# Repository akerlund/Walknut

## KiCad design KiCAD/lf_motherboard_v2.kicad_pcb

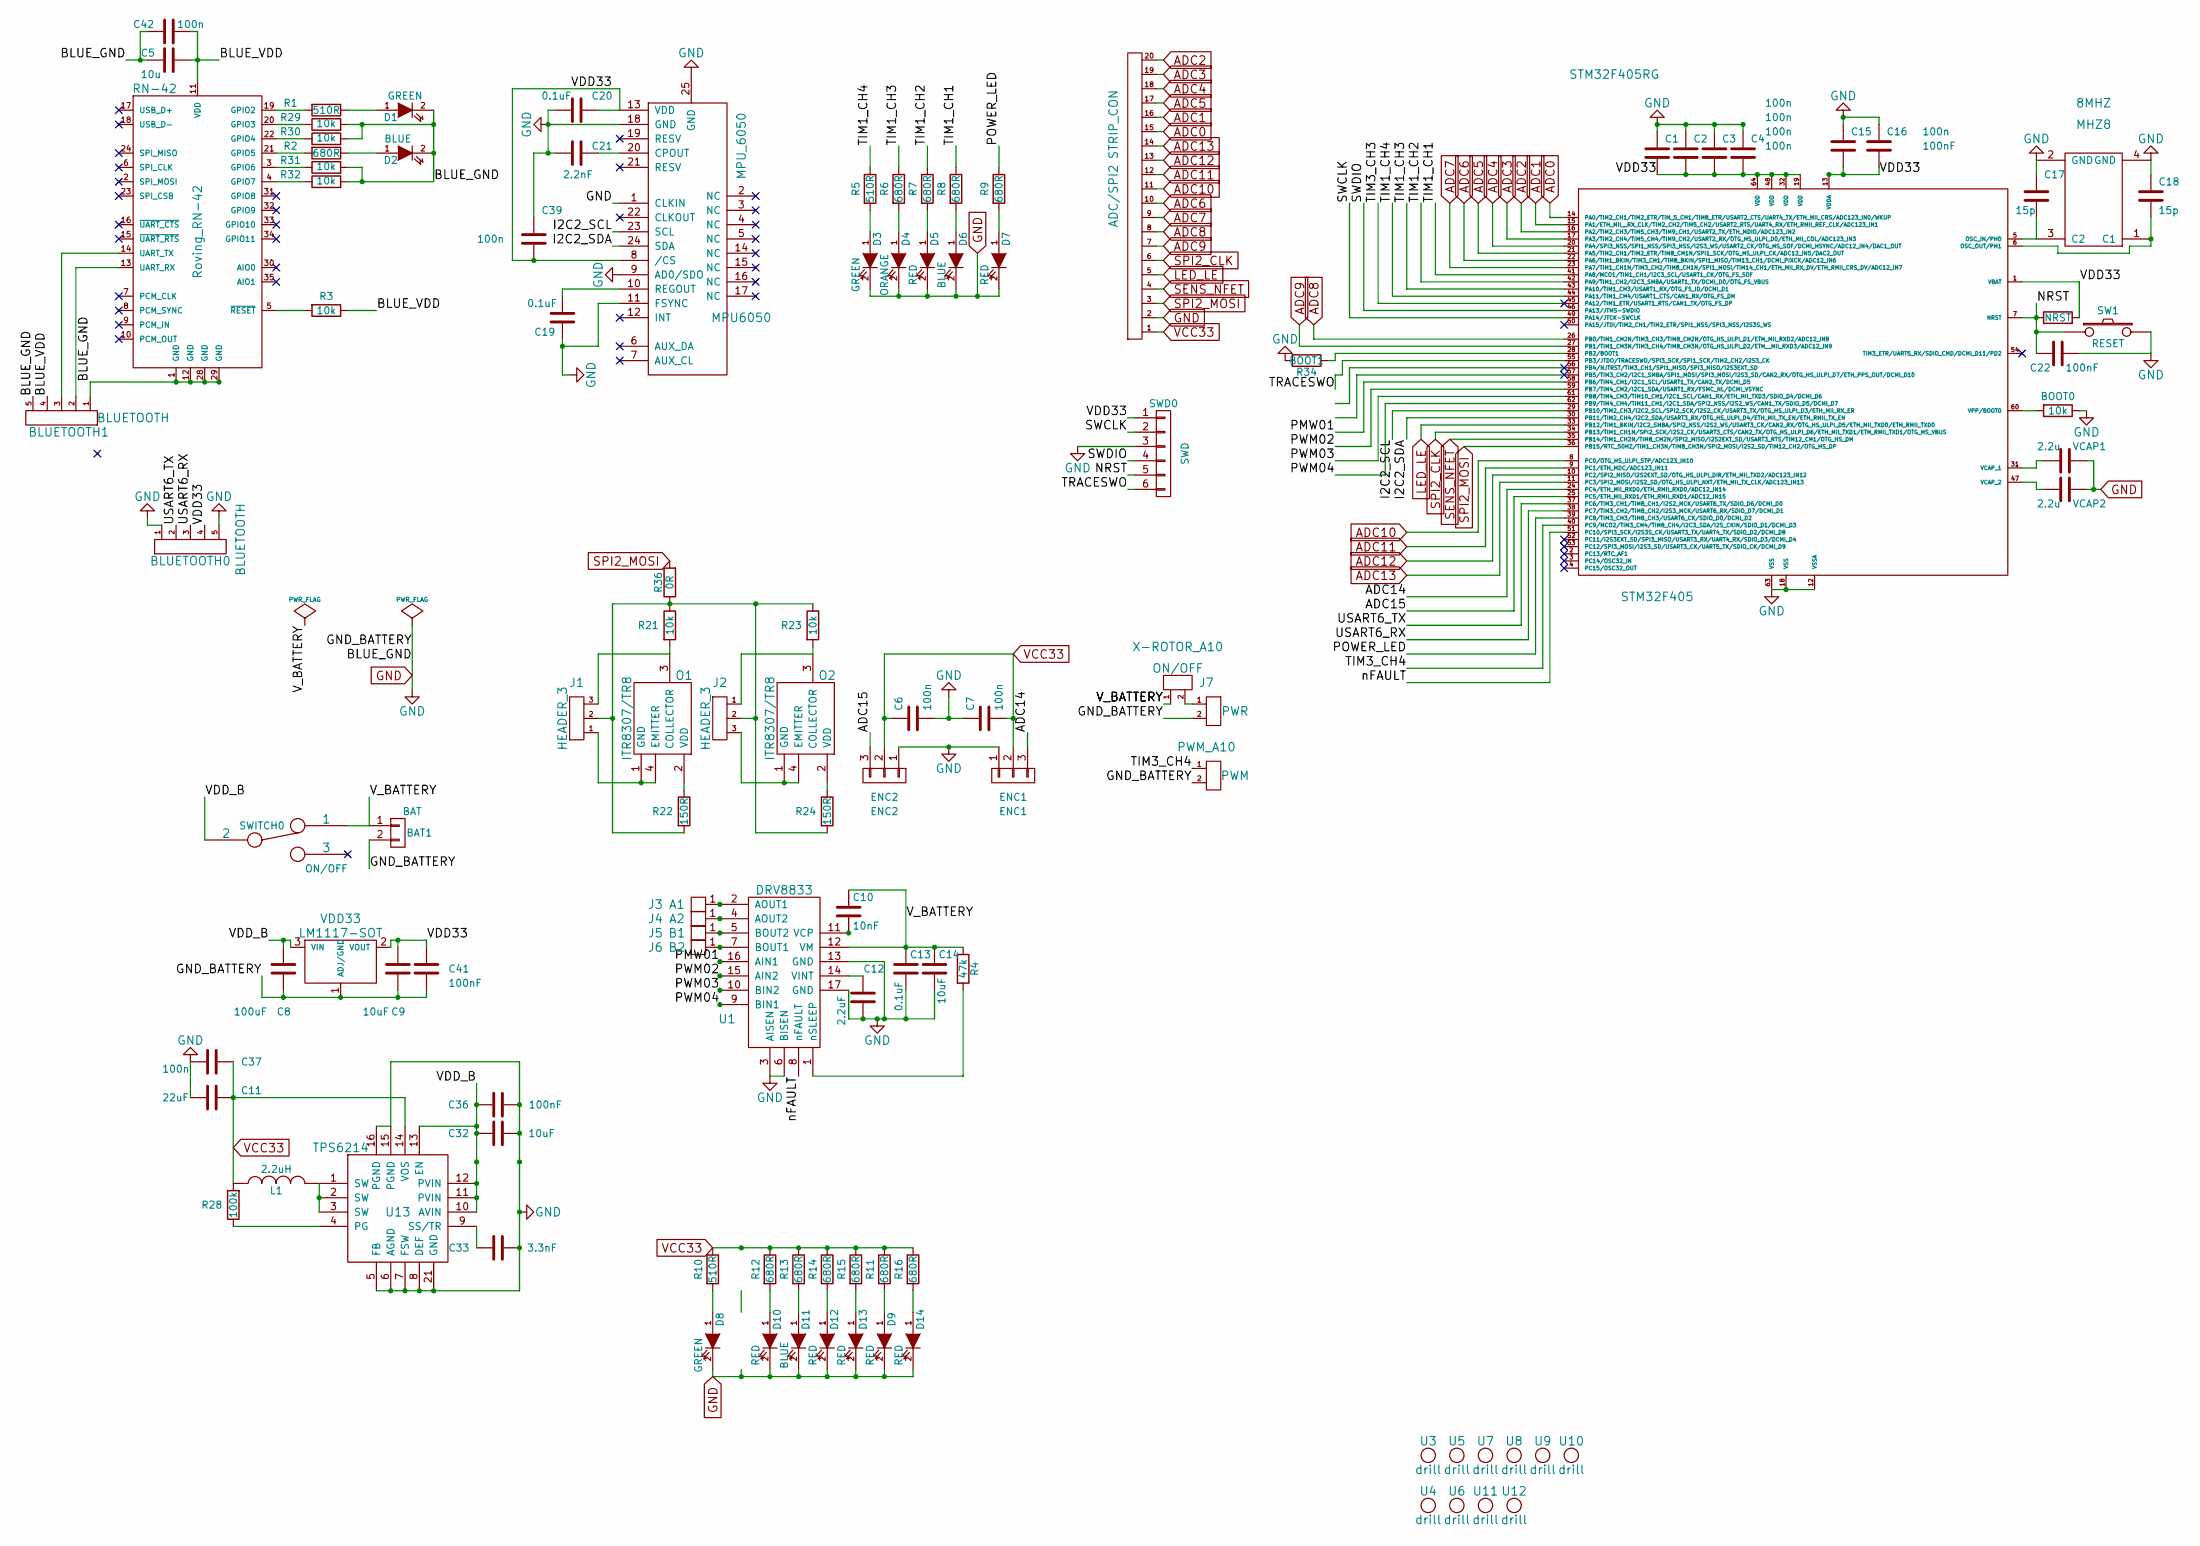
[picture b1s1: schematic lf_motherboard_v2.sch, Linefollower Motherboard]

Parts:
ADC/SPI2: STRIP_CON; panelmate_smd_20
BAT1: BAT; pin_socket_2
BLUETOOTH0, BLUETOOTH1: BLUETOOTH
BOOT0: 10k
C1, C2, C3, C4, C6, C7, C16: 100n; c_0603
C5: 10u; c_0603
C8: 100uF; c_0603
C9: 10uF; c_0603
C10: 10nF
C11: 22uF; c_elec_4x5.8
C12: 2.2uF
C13: 0.1uF
C14, C32: 10uF
C15: 100nF; c_0603
C17, C18: 15p; c_0603
C19, C20: 0.1uF; c_0603
C21: 2.2nF; c_0603
C22, C36, C41: 100nF
C33: 3.3nF
C37, C39, C42: 100n
D1, D3, D8: GREEN; Led_0603
D2, D6, D11: BLUE; Led_0603
D4: ORANGE; Led_0603
D5, D7, D9, D10, D12, D13, D14: RED; Led_0603
ENC1: ENC1; pin_socket_3
ENC2: ENC2; pin_socket_3
J1, J2: HEADER_3
J3: A1
J4: A2
J5: B1
J6: B2
J7: ON/OFF
L1: 2.2uH; inductor_smd_6.5x4.8mm
MHZ8: 8MHZ
MPU6050: MPU_6050
NRST1: NRST
O1, O2: ITR8307/TR8
PWM_A10: PWM
R1, R5, R10: 510R; r_0603
R2, R6, R7, R8, R9, R11, R12, R13, R14, R15, R16: 680R; r_0603
R3: 10k; r_0603
R4: 47k
R21, R23, R29, R30, R31, R32: 10k
R22, R24: 150R
R28: 100k
R34: BOOT1
R36: 0R
RN-42: Roving_RN-42; roving_rn-42
STM32F405: STM32F405RG; lqfp64
SW1: RESET
SWD0: SWD; s6b-ph-sm4-tb
SWITCH0: ON/OFF; switch_mmp122-r
U1: DRV8833
U3, U4, U5, U6, U7, U8, U9, U10, U11, U12: drill
U13: TPS6214
VCAP1, VCAP2: 2.2u; c_0603
VDD33: LM1117-SOT; sot223
X-ROTOR_A10: PWR

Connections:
/ADC14: ENC1.3, STM32F405.24 (PC4/ETH_MII_RXD0/ETH_RMII_RXD0/ADC12_IN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)
/ADC15: ENC2.3, STM32F405.25 (PC5/ETH_MII_RXD1/ETH_RMII_RXD1/ADC12_IN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)
/BLUE_VDD: BLUETOOTH1.4, C5.1, C42.2, R3.1, RN-42.11 (VDD)
/I2C2_SCL: MPU6050.23 (SCL), STM32F405.29 (PB10/TIM2_CH3/I2C2_SCL/SPI2_SCK/I2S2_CK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)
/I2C2_SDA: MPU6050.24 (SDA), STM32F405.30 (PB11/TIM2_CH4/I2C2_SDA/USART3_RX/OTG_HS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)
/NRST: C22.2, NRST1.1, STM32F405.7 (NRST), SW1.1, SWD0.5
/PMW01: STM32F405.58 (PB6/TIM4_CH1/I2C1_SCL/USART1_TX/CAN2_TX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), U1.16 (AIN1)
/POWER_LED: R9.1, STM32F405.39 (PC8/TIM3_CH3/TIM8_CH3/USART6_CK/SDIO_D0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)
/PWM02: STM32F405.59 (PB7/TIM4_CH2/I2C1_SDA/USART1_RX/FSMC_NL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), U1.15 (AIN2)
/PWM03: STM32F405.61 (PB8/TIM4_CH3/TIM10_CH1/I2C1_SCL/CAN1_RX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), U1.10 (BIN2)
/PWM04: STM32F405.62 (PB9/TIM4_CH4/TIM11_CH1/I2C1_SDA/SPI2_NS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), U1.9 (BIN1)
/SWCLK: STM32F405.49 (PA14/JTCK-SWCLK), SWD0.2
/SWDIO: STM32F405.46 (PA13/JTMS-SWDIO), SWD0.4
/TIM1_CH1: R8.1, STM32F405.41 (PA8/MCO1/TIM1_CH1/I2C3_SCL/USART1_CK/OT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)
/TIM1_CH2: R7.1, STM32F405.42 (PA9/TIM1_CH2/I2C3_SMBA/USART1_TX/DCMI_D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)
/TIM1_CH3: R6.1, STM32F405.43 (PA10/TIM1_CH3/USART1_RX/OTG_FS_ID/DCMI_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)
/TIM1_CH4: R5.1, STM32F405.44 (PA11/TIM1_CH4/USART1_CTS/CAN1_RX/OTG_FS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)
/TIM3_CH4: PWM_A10.1, STM32F405.40 (PC9/MCO2/TIM3_CH4/TIM8_CH4/I2C3_SDA/I2S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)
/TRACESWO: STM32F405.55 (PB3/JTDO/TRACESWO/SPI3_SCK/SPI1_SCK/TIM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), SWD0.6
/USART6_RX: BLUETOOTH0.3, STM32F405.38 (PC7/TIM3_CH2/TIM8_CH2/I2S3_MCK/USART6_R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)
/USART6_TX: BLUETOOTH0.2, STM32F405.37 (PC6/TIM3_CH1/TIM8_CH1/I2S2_MCK/USART6_T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)
/VDD33: BLUETOOTH0.4, C1.2, C2.2, C3.2, C4.2, C9.1, C15.2, C16.2, C20.1, C39.2, C41.1, MPU6050.8 (/CS), MPU6050.13 (VDD), NRST1.2, STM32F405.1 (VBAT), STM32F405.13 (VDDA), STM32F405.19 (VDD), STM32F405.32 (VDD), STM32F405.48 (VDD), STM32F405.64 (VDD), SWD0.1, VDD33.2 (VOUT); also elsewhere on the board
/VDD_B: C8.1, C32.1, C36.1, SWITCH0.2, U13.10 (AVIN), U13.11 (PVIN), U13.12 (PVIN), U13.13 (EN), VDD33.3 (VIN)
/V_BATTERY: BAT1.1, C10.1, C13.1, C14.1, J7.1, R4.1, SWITCH0.1, U1.12 (VM)
/nFAULT: STM32F405.51 (PC10/SPI3_SCK/I2S3S_CK/USART3_TX/UART4_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), U1.8 (nFAULT)
ADC0: ADC/SPI2.15, STM32F405.14 (PA0/TIM2_CH1/TIM2_ETR/TIM_5_CH1/TIM8_ET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)
ADC1: ADC/SPI2.16, STM32F405.15 (PA1/ETH_MII__RX_CLK/TIM2_CH2/TIM5_CH2/U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)
ADC2: ADC/SPI2.20, STM32F405.16 (PA2/TIM2_CH3/TIM5_CH3/TIM9_CH1/USART2_T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)
ADC3: ADC/SPI2.19, STM32F405.17 (PA3/TIM2_CH4/TIM5_CH4/TIM9_CH2/USART2_R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)
ADC4: ADC/SPI2.18, STM32F405.20 (PA4/SPI3_NSS/SPI1_NSS/SPI3_NSS/I2S3_WS/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)
ADC5: ADC/SPI2.17, STM32F405.21 (PA5/TIM2_CH1/TIM2_ETR/TIM8_CH1N/SPI1_SC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)
ADC6: ADC/SPI2.10, STM32F405.22 (PA6/TIM1_BKIN/TIM3_CH1/TIM8_BKIN/SPI1_M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)
ADC7: ADC/SPI2.9, STM32F405.23 (PA7/TIM1_CH1N/TIM3_CH2/TIM8_CH1N/SPI1_M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)
ADC8: ADC/SPI2.8, STM32F405.26 (PB0/TIM1_CH2N/TIM3_CH3/TIM8_CH2N/OTG_HS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)
ADC9: ADC/SPI2.7, STM32F405.27 (PB1/TIM1_CH3N/TIM3_CH4/TIM8_CH3N/OTG_HS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)
ADC10: ADC/SPI2.11, STM32F405.8 (PC0/OTG_HS_ULPI_STP/ADC123_IN10)
ADC11: ADC/SPI2.12, STM32F405.9 (PC1/ETH_MDC/ADC123_IN11)
ADC12: ADC/SPI2.13, STM32F405.10 (PC2/SPI2_MISO/I2S2EXT_SD/OTG_HS_ULPI_DI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)
ADC13: ADC/SPI2.14, STM32F405.11 (PC3/SPI2_MOSI/I2S2_SD/OTG_HS_ULPI_NXT/E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)
GND: ADC/SPI2.2, BAT1.2, BLUETOOTH0.1, BLUETOOTH0.5, BLUETOOTH1.1, BLUETOOTH1.5, BOOT0.1, C1.1, C2.1, C3.1, C4.1, C5.2, C6.2, C7.1, C8.2, C9.2, C11.2, C12.2, C13.2, C14.2, C15.1, C16.1, C17.1, C18.1, C19.2, C20.2, C21.2, C22.1, C32.2, C33.1, C36.2, C37.2, C39.1, C41.2, C42.1, D1.2 (K), D2.2 (K), D3.2 (K), D4.2 (K), D5.2 (K), D6.2 (K), D7.2 (K), D8.2 (K), D9.2 (K), D10.2 (K), D11.2 (K), D12.2 (K), D13.2 (K), D14.2 (K), ENC1.1, ENC2.1, MHZ8.2 (GND), MHZ8.4 (GND), MPU6050.1 (CLKIN), MPU6050.9 (AD0/SDO), MPU6050.11 (FSYNC), MPU6050.18 (GND), MPU6050.25 (GND), PWM_A10.2, R29.2, R30.2, R31.2, R32.2, R34.2, RN-42.1 (GND), RN-42.12 (GND), RN-42.28 (GND), RN-42.29 (GND), STM32F405.12 (VSSA), STM32F405.18 (VSS), STM32F405.63 (VSS), SW1.2, SWD0.3, U1.3 (AISEN), U1.6 (BISEN), U1.13 (GND), U1.17 (GND), U13.5 (FB), U13.6 (AGND), U13.7 (FSW), U13.8 (DEF), U13.15 (PGND), U13.16 (PGND), U13.21 (GND), VCAP1.1, VCAP2.1, VDD33.1 (ADJ/GND), X-ROTOR_A10.2; also elsewhere on the board
LED_LE: ADC/SPI2.5, STM32F405.33 (PB12/TIM1_BKIN/I2C2_SMBA/SPI2_NSS/I2S2_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)
unnamed: BLUETOOTH1.2, RN-42.13 (UART_RX)
unnamed: BLUETOOTH1.3, RN-42.14 (UART_TX)
unnamed: BOOT0.2, STM32F405.60 (VPP/BOOT0)
unnamed: C10.2, U1.11 (VCP)
unnamed: C12.1, U1.14 (VINT)
unnamed: C17.2, MHZ8.3 (C2), STM32F405.5 (OSC_IN/PH0)
unnamed: C18.2, MHZ8.1 (C1), STM32F405.6 (OSC_OUT/PH1)
unnamed: C19.1, MPU6050.10 (REGOUT)
unnamed: C21.1, MPU6050.20 (CPOUT)
unnamed: C33.2, U13.9 (SS/TR)
unnamed: D1.1 (A), R1.1
unnamed: D2.1 (A), R2.1
unnamed: D3.1 (A), R5.2
unnamed: D4.1 (A), R6.2
unnamed: D5.1 (A), R7.2
unnamed: D6.1 (A), R8.2
unnamed: D7.1 (A), R9.2
unnamed: D8.1 (A), R10.2
unnamed: D9.1 (A), R11.2
unnamed: D10.1 (A), R12.2
unnamed: D11.1 (A), R13.2
unnamed: D12.1 (A), R14.2
unnamed: D13.1 (A), R15.2
unnamed: D14.1 (A), R16.2
unnamed: J1.1, O1.1 (GND), O1.4 (EMITTER)
unnamed: J1.2, J2.2, R21.1, R22.2, R23.1, R24.2, R36.1
unnamed: J1.3, O1.3 (COLLECTOR), R21.2
unnamed: J2.1, O2.3 (COLLECTOR), R23.2
unnamed: J2.3, O2.1 (GND), O2.4 (EMITTER)
unnamed: J3.1, U1.2 (AOUT1)
unnamed: J4.1, U1.4 (AOUT2)
unnamed: J5.1, U1.5 (BOUT2)
unnamed: J6.1, U1.7 (BOUT1)
unnamed: J7.2, X-ROTOR_A10.1
unnamed: L1.2, U13.1 (SW), U13.2 (SW), U13.3 (SW)
unnamed: O1.2 (VDD), R22.1
unnamed: O2.2 (VDD), R24.1
unnamed: R1.2, RN-42.19 (GPIO2)
unnamed: R2.2, RN-42.21 (GPIO5)
unnamed: R3.2, RN-42.5 (~RESET)
unnamed: R4.2, U1.1 (nSLEEP)
unnamed: R28.1, U13.4 (PG)
unnamed: R29.1, RN-42.20 (GPIO3)
unnamed: R30.1, RN-42.22 (GPIO4)
unnamed: R31.1, RN-42.3 (GPIO6)
unnamed: R32.1, RN-42.4 (GPIO7)
unnamed: R34.1, STM32F405.28 (PB2/BOOT1)
unnamed: STM32F405.31 (VCAP_1), VCAP1.2
unnamed: STM32F405.47 (VCAP_2), VCAP2.2
SENS_NFET: ADC/SPI2.4, STM32F405.35 (PB14/TIM1_CH2N/TIM8_CH2N/SPI2_MISO/I2S2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)
SPI2_CLK: ADC/SPI2.6, STM32F405.34 (PB13/TIM1_CH1N/SPI2_SCK/I2S2_CK/USART3_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)
SPI2_MOSI: ADC/SPI2.3, R36.2, STM32F405.36 (PB15/RTC_50HZ/TIM1_CH3N/TIM8_CH3N/SPI2_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)
VCC33: ADC/SPI2.1, C6.1, C7.2, C11.1, C37.1, ENC1.2, ENC2.2, L1.1, R10.1, R11.1, R12.1, R13.1, R14.1, R15.1, R16.1, R28.2, U13.14 (VOS)

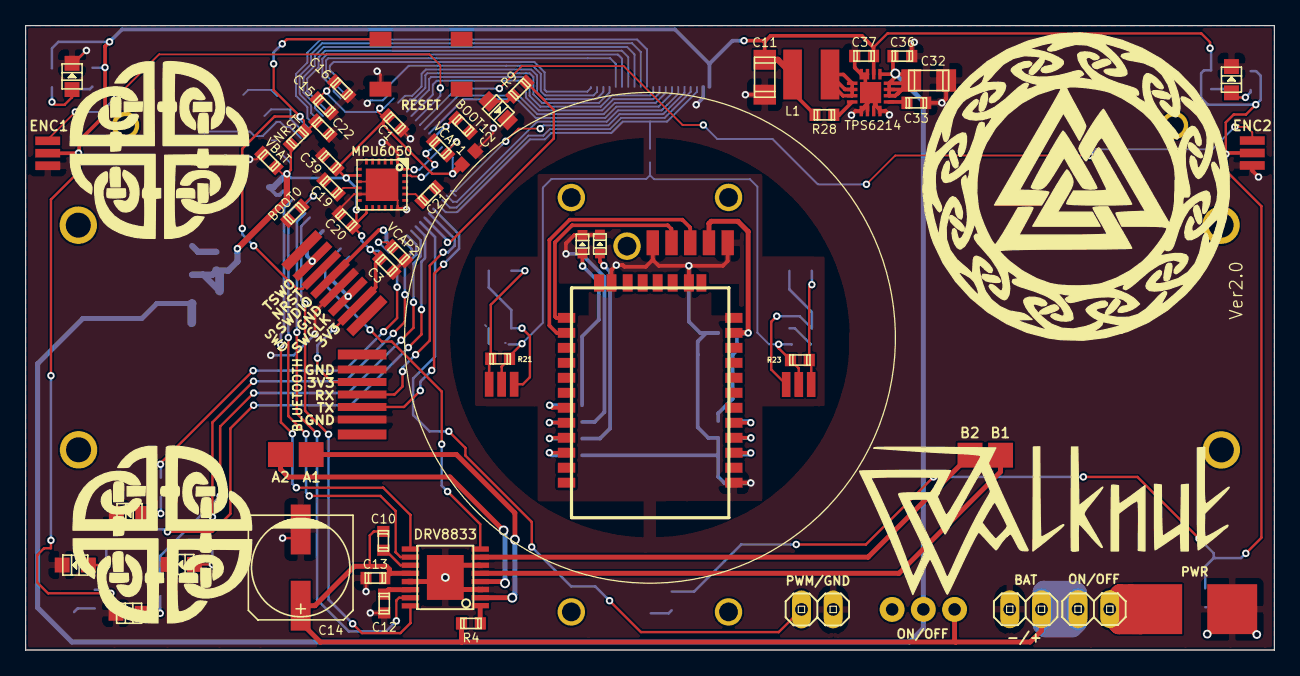
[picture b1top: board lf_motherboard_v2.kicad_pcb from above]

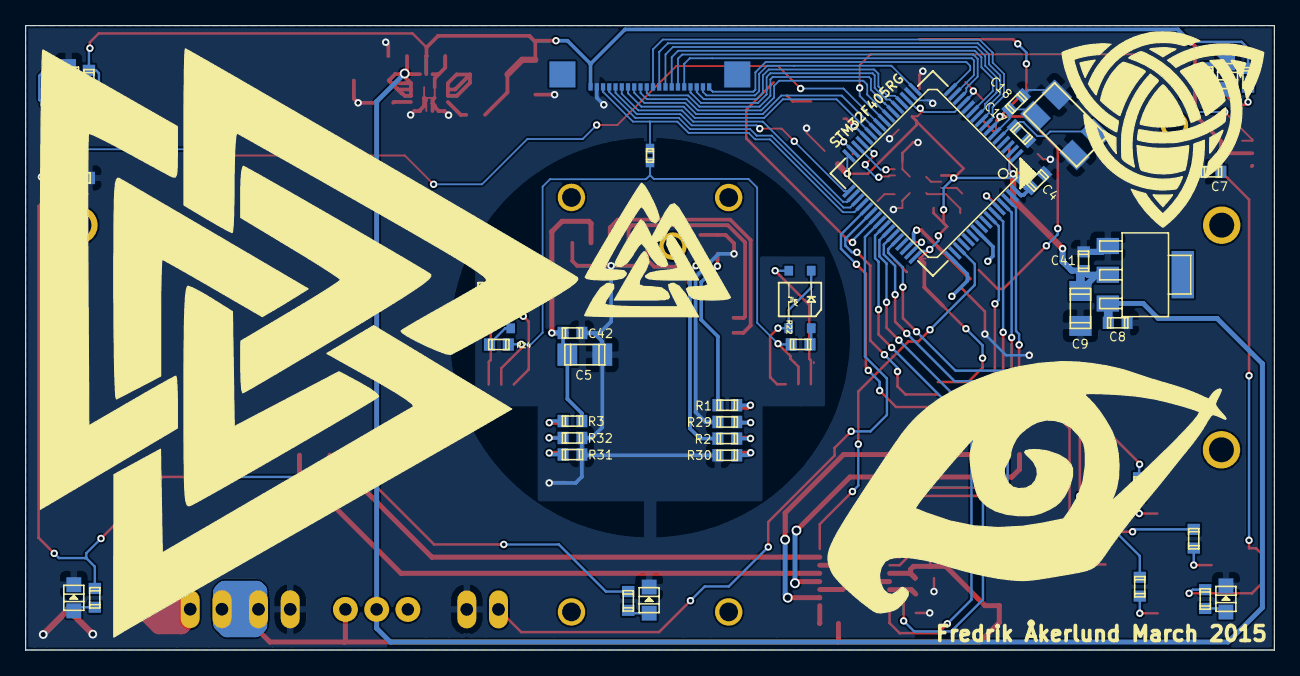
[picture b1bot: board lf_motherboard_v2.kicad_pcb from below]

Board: 2 copper layers, 100.0 x 50.0 mm, 113 parts (42 on the bottom side), 94 nets.

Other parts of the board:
VBAT1: VBAT; r_0603

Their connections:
/VDD33: VBAT1.1; also elsewhere on the board
GND: VBAT1.2; also elsewhere on the board

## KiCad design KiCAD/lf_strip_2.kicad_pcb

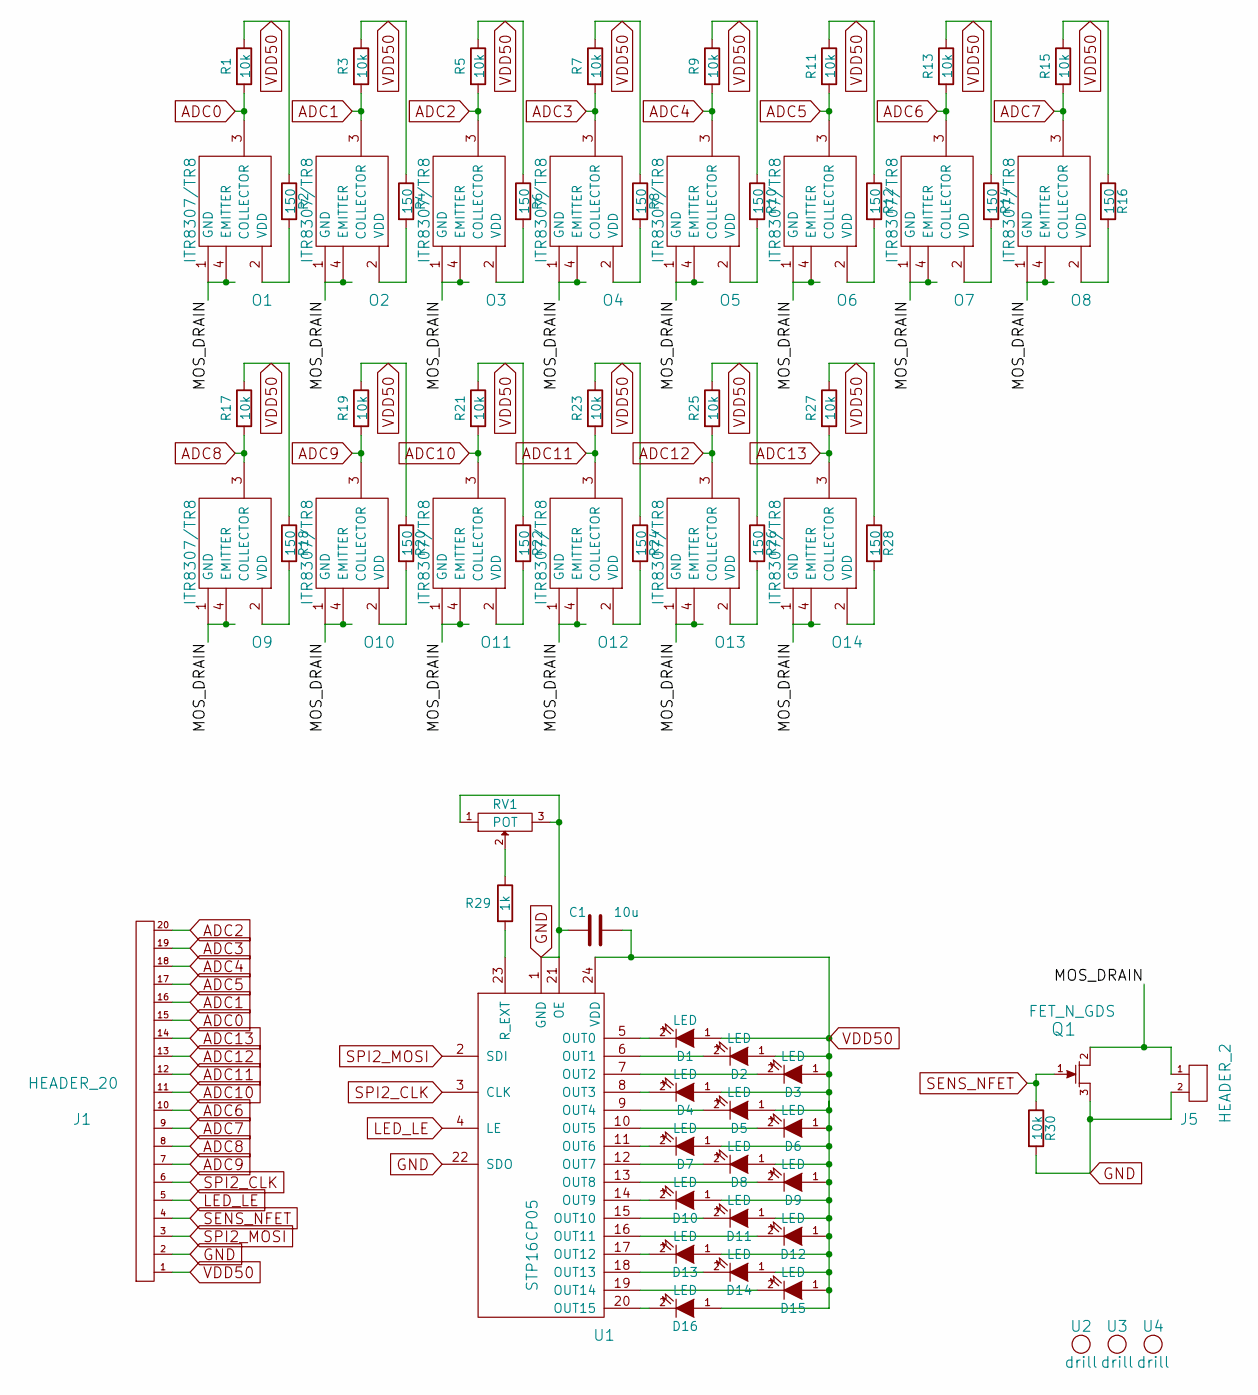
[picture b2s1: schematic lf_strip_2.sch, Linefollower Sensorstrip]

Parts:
C1: 10u
D1, D2, D3, D4, D5, D6, D7, D8, D9, D10, D11, D12, D13, D14, D15, D16: LED
J1: HEADER_20
J5: HEADER_2; pin_strip_2
O1, O2, O3, O4, O5, O6, O7, O8, O9, O10, O11, O12, O13, O14: ITR8307/TR8; w_freaquency_smd_opto_ITR8307
Q1: FET_N_GDS
R1, R3, R5, R7, R9, R11, R13, R15, R17, R19, R21, R23, R25, R27, R30: 10k; r_0603
R2, R4, R6, R8, R10, R12, R14, R16, R18, R20, R22, R24, R26, R28: 150; r_0603
R29: 1k
RV1: POT
U1: STP16CP05
U2, U3, U4: drill

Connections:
/MOS_DRAIN: J5.1, O1.1 (GND), O1.4 (EMITTER), O2.1 (GND), O2.4 (EMITTER), O3.1 (GND), O3.4 (EMITTER), O4.1 (GND), O4.4 (EMITTER), O5.1 (GND), O5.4 (EMITTER), O6.1 (GND), O6.4 (EMITTER), O7.1 (GND), O7.4 (EMITTER), O8.1 (GND), O8.4 (EMITTER), O9.1 (GND), O9.4 (EMITTER), O10.1 (GND), O10.4 (EMITTER), O11.1 (GND), O11.4 (EMITTER), O12.1 (GND), O12.4 (EMITTER), O13.1 (GND), O13.4 (EMITTER), O14.1 (GND), O14.4 (EMITTER), Q1.2 (D)
ADC0: J1.15, O1.3 (COLLECTOR), R1.2
ADC1: J1.16, O2.3 (COLLECTOR), R3.2
ADC2: J1.20, O3.3 (COLLECTOR), R5.2
ADC3: J1.19, O4.3 (COLLECTOR), R7.2
ADC4: J1.18, O5.3 (COLLECTOR), R9.2
ADC5: J1.17, O6.3 (COLLECTOR), R11.2
ADC6: J1.10, O7.3 (COLLECTOR), R13.2
ADC7: J1.9, O8.3 (COLLECTOR), R15.2
ADC8: J1.8, O9.3 (COLLECTOR), R17.2
ADC9: J1.7, O10.3 (COLLECTOR), R19.2
ADC10: J1.11, O11.3 (COLLECTOR), R21.2
ADC11: J1.12, O12.3 (COLLECTOR), R23.2
ADC12: J1.13, O13.3 (COLLECTOR), R25.2
ADC13: J1.14, O14.3 (COLLECTOR), R27.2
GND: C1.2, J1.2, J5.2, Q1.3 (S), R30.2, RV1.1, RV1.3, U1.1 (GND), U1.21 (OE), U1.22 (SDO)
LED_LE: J1.5, U1.4 (LE)
unnamed: D1.2 (K), U1.5 (OUT0)
unnamed: D2.2 (K), U1.6 (OUT1)
unnamed: D3.2 (K), U1.7 (OUT2)
unnamed: D4.2 (K), U1.8 (OUT3)
unnamed: D5.2 (K), U1.9 (OUT4)
unnamed: D6.2 (K), U1.10 (OUT5)
unnamed: D7.2 (K), U1.11 (OUT6)
unnamed: D8.2 (K), U1.12 (OUT7)
unnamed: D9.2 (K), U1.13 (OUT8)
unnamed: D10.2 (K), U1.14 (OUT9)
unnamed: D11.2 (K), U1.15 (OUT10)
unnamed: D12.2 (K), U1.16 (OUT11)
unnamed: D13.2 (K), U1.17 (OUT12)
unnamed: D14.2 (K), U1.18 (OUT13)
unnamed: D15.2 (K), U1.19 (OUT14)
unnamed: D16.2 (K), U1.20 (OUT15)
unnamed: O1.2 (VDD), R2.2
unnamed: O2.2 (VDD), R4.2
unnamed: O3.2 (VDD), R6.2
unnamed: O4.2 (VDD), R8.2
unnamed: O5.2 (VDD), R10.2
unnamed: O6.2 (VDD), R12.2
unnamed: O7.2 (VDD), R14.2
unnamed: O8.2 (VDD), R16.2
unnamed: O9.2 (VDD), R18.2
unnamed: O10.2 (VDD), R20.2
unnamed: O11.2 (VDD), R22.2
unnamed: O12.2 (VDD), R24.2
unnamed: O13.2 (VDD), R26.2
unnamed: O14.2 (VDD), R28.2
unnamed: R29.1, RV1.2
unnamed: R29.2, U1.23 (R_EXT)
SENS_NFET: J1.4, Q1.1 (G), R30.1
SPI2_CLK: J1.6, U1.3 (CLK)
SPI2_MOSI: J1.3, U1.2 (SDI)
VDD50: C1.1, D1.1 (A), D2.1 (A), D3.1 (A), D4.1 (A), D5.1 (A), D6.1 (A), D7.1 (A), D8.1 (A), D9.1 (A), D10.1 (A), D11.1 (A), D12.1 (A), D13.1 (A), D14.1 (A), D15.1 (A), D16.1 (A), J1.1, R1.1, R2.1, R3.1, R4.1, R5.1, R6.1, R7.1, R8.1, R9.1, R10.1, R11.1, R12.1, R13.1, R14.1, R15.1, R16.1, R17.1, R18.1, R19.1, R20.1, R21.1, R22.1, R23.1, R24.1, R25.1, R26.1, R27.1, R28.1, U1.24 (VDD)

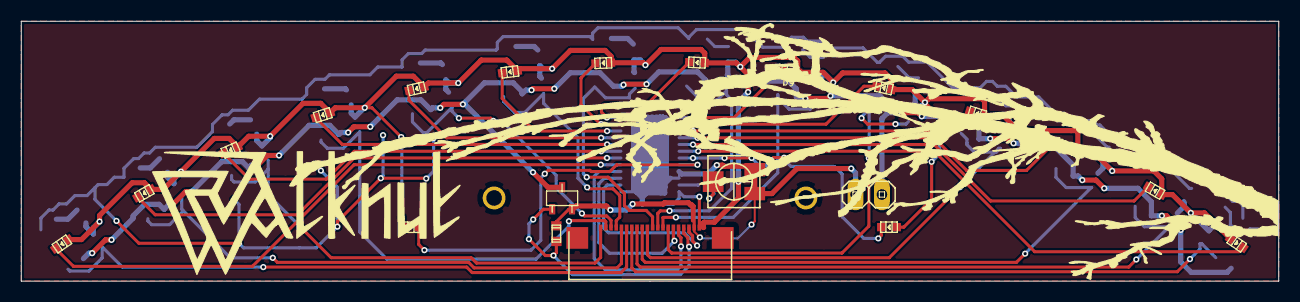
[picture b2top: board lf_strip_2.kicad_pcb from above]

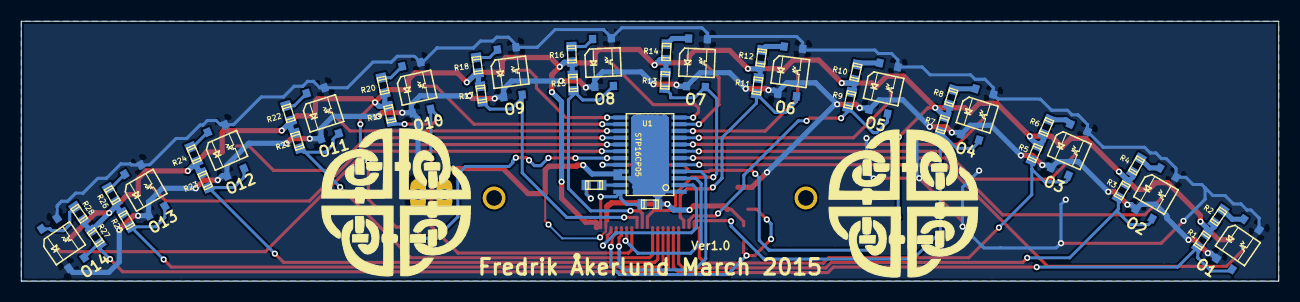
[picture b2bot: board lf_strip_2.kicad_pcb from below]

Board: 2 copper layers, 121.0 x 25.0 mm, 69 parts (45 on the bottom side), 53 nets.

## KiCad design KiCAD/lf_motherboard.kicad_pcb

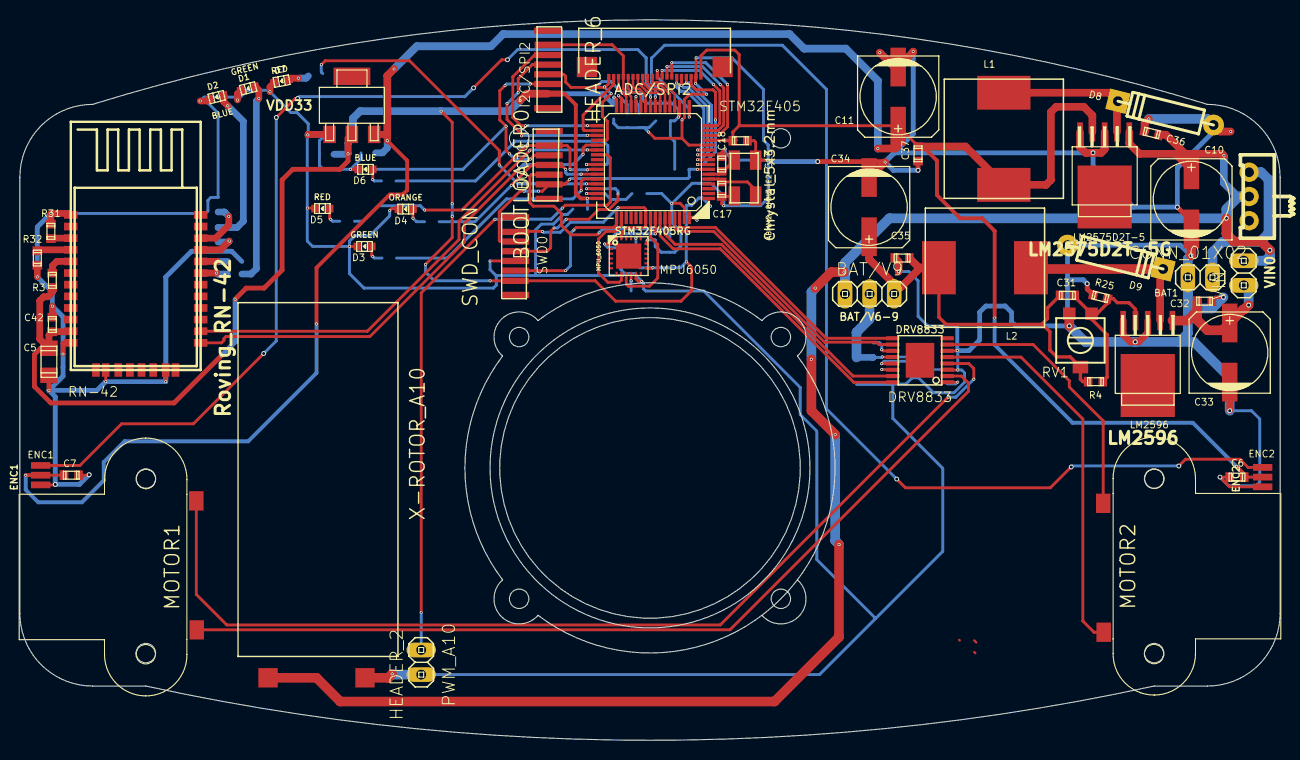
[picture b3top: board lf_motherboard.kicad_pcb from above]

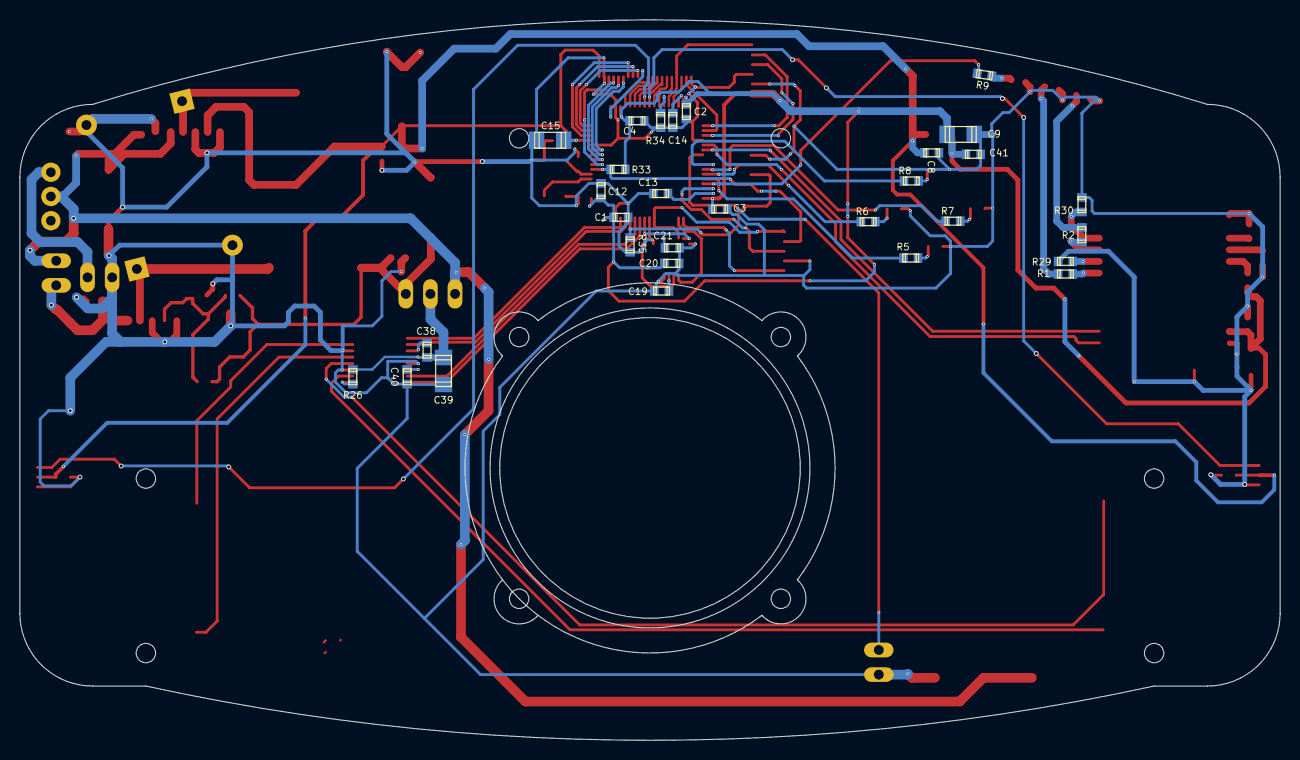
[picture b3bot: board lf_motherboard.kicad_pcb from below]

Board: 2 copper layers, 130.0 x 74.3 mm, 85 parts (30 on the bottom side), 81 nets.

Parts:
ABMM2-8MHZ-E2: Chrystal_5x3.2mm; Chrystal
ADC/SPI2: STRIP_CON; smd_jst_FLZ_20pin
BAT1: CONN_01X02; pinhead-1X02
BAT/V6-9: BAT/V9; pinhead-1X03
BOOT0: BOOTLOADER0; MicroJST_5p
C1, C2, C3, C4, C6, C7, C12, C16, C36, C37, C42: 100n; c_0603
C5: 10u; c_1206
C8: 100uF; c_0603
C9, C15, C39: 10uF; c_1206
C10, C34: 220uF; c_elec_8x6.5
C11: 330uF; c_elec_8x6.5
C13, C14: 2.2u; c_0603
C17, C18: 15p; c_0603
C19, C20: 0.1uF; c_0603
C21: 2.2nF; c_0603
C31: 4.7nF; c_0603
C32, C35, C41: 100nF; c_0603
C33: 470uF; c_elec_8x6.5
C38: 10nF; c_0603
C40: 2.2uF; c_0603
D1, D3: GREEN; Led_0603
D2, D6: BLUE; Led_0603
D4: ORANGE; Led_0603
D5, D7: RED; Led_0603
D8, D9: SCHOTTKY; DIODE_1
DRV8833: DRV8833; SSOP17_W
ENC1: ENC1; smd_encoder_3pin_1mm
ENC2: ENC2; smd_encoder_3pin_1mm
I2C/SPI2: HEADER_6; JST_Micro6Pin
J13: MOTOR1; Pololu_Motor_Bracket
J14: MOTOR2; Pololu_Motor_Bracket
L1: 330uH; coilcraft_12.3x12.3mm
L2: 68uH; coilcraft_12.3x12.3mm
LM2575D2T-5: LM2575D2T-5G; d-pak-5
LM2596: LM2596; d-pak-5
MPU6050: MPU_6050; qfn-24
PWM_A10: HEADER_2; pinhead-1X02
R1, R5: 510R; r_0603
R2, R6, R7, R8, R9: 680R; r_0603
R3, R29, R30, R31, R32, R34, R35: 10k; r_0603
R4: 6.33k; r_0603
R25: 1k; r_0603
R26, R33: 3.3k; r_0603
RN-42: Roving_RN-42; roving_rn-42
RV1: 10k POT; trim_bi_23b
STM32F405: STM32F405RG; lqfp64
SWD0: SWD_CON; JST_Micro6Pin
SWITCH0: SWITCH_INV; switch_mmp122-r
VDD33: LM1117-SOT; sot223
VIN0: VIN; pinhead-1X02
X-ROTOR_A10: HEADER_2; X-Rotor_10A

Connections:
/ADC14: ENC2.3, STM32F405.24
/ADC15: ENC1.3, STM32F405.25
/BOOT0: BOOT0.2, R35.1, STM32F405.60
/BOOT1: R34.1, STM32F405.28
/DRV3_OUT_A1: DRV8833.2, J13.1
/DRV3_OUT_A2: DRV8833.4, J13.2
/DRV3_OUT_B1: DRV8833.5, J14.2
/DRV3_OUT_B2: DRV8833.7, J14.1
/NRST: BOOT0.1, R33.2, STM32F405.7, SWD0.5
/POWER_LED: R9.1, STM32F405.45
/PWM01: DRV8833.16, STM32F405.58
/PWM02: DRV8833.15, STM32F405.59
/PWM03: DRV8833.10, STM32F405.61
/PWM04: DRV8833.9, STM32F405.62
/PWM_LED0: R8.1, STM32F405.41
/PWM_LED1: BOOT0.5, R7.1, STM32F405.42
/PWM_LED2: BOOT0.3, R6.1, STM32F405.43
/PWM_LED3: R5.1, STM32F405.44
/SPI3_MISO: MPU6050.9, STM32F405.56
/SPI3_MOSI: MPU6050.24, STM32F405.57
/SPI3_NSS: MPU6050.8, STM32F405.50
/SPI3_SCK: MPU6050.23, STM32F405.55, SWD0.6
/SWCLK: STM32F405.49, SWD0.2
/SWDIO: STM32F405.46, SWD0.4
/TIM3_CH3: PWM_A10.1, STM32F405.39
/USART6_RX: RN-42.14, STM32F405.38
/USART6_TX: RN-42.13, STM32F405.37
/VDD33: C1.2, C2.2, C3.2, C4.2, C5.1, C9.1, C12.1, C20.1, C41.1, C42.2, I2C/SPI2.6, MPU6050.13, R3.1, R33.1, RN-42.11, STM32F405.1, STM32F405.19, STM32F405.32, STM32F405.48, STM32F405.64, SWD0.1, VDD33.2
/VDD90: BAT/V6-9.1, C31.1, C34.1, C35.2, L2.2, R4.1, RV1.2
/VDD_B: BAT/V6-9.3, C10.1, C36.1, LM2575D2T-5.1, SWITCH0.2, VIN0.1, X-ROTOR_A10.1
/V_BATTERY: BAT1.1, SWITCH0.3
ADC0: ADC/SPI2.14, STM32F405.14
ADC1: ADC/SPI2.13, STM32F405.15
ADC2: ADC/SPI2.12, STM32F405.16
ADC3: ADC/SPI2.11, STM32F405.17
ADC4: ADC/SPI2.10, STM32F405.20
ADC5: ADC/SPI2.9, STM32F405.21
ADC6: ADC/SPI2.8, STM32F405.22
ADC7: ADC/SPI2.7, STM32F405.23
ADC8: ADC/SPI2.6, STM32F405.26
ADC9: ADC/SPI2.5, STM32F405.27
ADC10: ADC/SPI2.18, STM32F405.8
ADC11: ADC/SPI2.17, STM32F405.9
ADC12: ADC/SPI2.16, STM32F405.10
ADC13: ADC/SPI2.15, STM32F405.11
GND: ABMM2-8MHZ-E2.2, ABMM2-8MHZ-E2.4, ADC/SPI2.19, BAT1.2, BOOT0.4, C1.1, C2.1, C3.1, C4.1, C5.2, C6.2, C7.1, C8.2, C9.2, C10.2, C11.2, C12.2, C13.1, C14.1, C15.1, C16.1, C17.1, C18.1, C19.2, C20.2, C21.2, C32.2, C33.2, C34.2, C35.1, C36.2, C37.2, C39.1, C40.1, C41.2, C42.1, D1.2, D2.2, D3.2, D4.2, D5.2, D6.2, D7.2, D8.1, D9.1, DRV8833.3, DRV8833.6, DRV8833.13, ENC1.1, ENC2.1, I2C/SPI2.5, LM2575D2T-5.3, LM2575D2T-5.5, LM2596.3, LM2596.5, MPU6050.1, MPU6050.11, MPU6050.18, PWM_A10.2, R25.2, R29.2, R30.2, R31.2, R32.2, R34.2, R35.2, RN-42.1, RN-42.12, RN-42.28, RN-42.29, RV1.3, STM32F405.12, STM32F405.18, STM32F405.63, SWD0.3, VDD33.1, X-ROTOR_A10.2
LED_LE: ADC/SPI2.3, STM32F405.30
unnamed: ABMM2-8MHZ-E2.1, C18.2, STM32F405.6
unnamed: ABMM2-8MHZ-E2.3, C17.2, STM32F405.5
unnamed: BAT/V6-9.2, C38.1, C39.2, DRV8833.12, R26.1
unnamed: C13.2, STM32F405.47
unnamed: C14.2, STM32F405.31
unnamed: C19.1, MPU6050.10
unnamed: C21.1, MPU6050.20
unnamed: C31.2, LM2596.4, R4.2, R25.1, RV1.1
unnamed: C32.1, C33.1, LM2596.1, VIN0.2
unnamed: C38.2, DRV8833.11
unnamed: C40.2, DRV8833.14
unnamed: D1.1, R1.1
unnamed: D2.1, R2.1
unnamed: D3.1, R5.2
unnamed: D4.1, R6.2
unnamed: D5.1, R7.2
unnamed: D6.1, R8.2
unnamed: D7.1, R9.2
unnamed: D8.2, L1.1, LM2575D2T-5.2
unnamed: D9.2, L2.1, LM2596.2
unnamed: DRV8833.1, R26.2
unnamed: R1.2, RN-42.19
unnamed: R2.2, RN-42.21
unnamed: R3.2, RN-42.5
unnamed: R29.1, RN-42.20
unnamed: R30.1, RN-42.22
unnamed: R31.1, RN-42.3
unnamed: R32.1, RN-42.4
SENS_NFET: ADC/SPI2.2, STM32F405.34
SPI2_CLK: ADC/SPI2.4, I2C/SPI2.1, STM32F405.29
SPI2_MISO: I2C/SPI2.3, STM32F405.35
SPI2_MOSI: ADC/SPI2.1, I2C/SPI2.4, STM32F405.36
SPI2_NSS: I2C/SPI2.2, STM32F405.33
VDD50: ADC/SPI2.20, C6.1, C7.2, C8.1, C11.1, C15.2, C16.2, C37.1, ENC1.2, ENC2.2, L1.2, LM2575D2T-5.4, STM32F405.13, VDD33.3

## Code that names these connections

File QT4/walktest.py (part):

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		self.label_adc14.setText(_translate("MainWindow", "0", None))
		self.label_adc13.setText(_translate("MainWindow", "0", None))
		self.label_adc3.setText(_translate("MainWindow", "0", None))
		self.label_37.setText(_translate("MainWindow", "ADC13", None))
		self.label_38.setText(_translate("MainWindow", "ADC14", None))
		self.label_adc5.setText(_translate("MainWindow", "0", None))
		self.label_36.setText(_translate("MainWindow", "ADC12", None))
		self.label_29.setText(_translate("MainWindow", "ADC5", None))
		self.label_25.setText(_translate("MainWindow", "ADC2", None))
		self.label_26.setText(_translate("MainWindow", "ADC3", None))
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		self.label_31.setText(_translate("MainWindow", "ADC7", None))
		self.label_30.setText(_translate("MainWindow", "ADC6", None))
		self.label_33.setText(_translate("MainWindow", "ADC9", None))
		self.label_35.setText(_translate("MainWindow", "ADC11", None))
		self.label_34.setText(_translate("MainWindow", "ADC10", None))
		self.label_adc1.setText(_translate("MainWindow", "0", None))
		self.label_54.setText(_translate("MainWindow", "Ki", None))
		self.label_kp.setText(_translate("MainWindow", "0", None))
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
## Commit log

2016-06-08 Second commit
